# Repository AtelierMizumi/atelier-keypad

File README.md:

# Atelier6K Keypad Project
The Atelier6K is a 6 keys keypad with 3 additional button designed for playing osu! or to be used as small macropad
+ Hotswapable
+ Per switch RGB + Bottom Case RGB
+ Acrylic Case
+ QMK Firmware with VIA compable (Keybinding, Light Control ...)

# Preview images

## PCB front view

## PCB back view

## Case

+ 7$: Fuse, Led, Switch, Bolts, Keycap, USB C Female connector, Rubber Feet
+ 5$: Atmega32u4
+ 5$: Acrylic Case
+ 3$: PCB printing
+ 2$: USB Cable

$40 to be expected

# Sketch

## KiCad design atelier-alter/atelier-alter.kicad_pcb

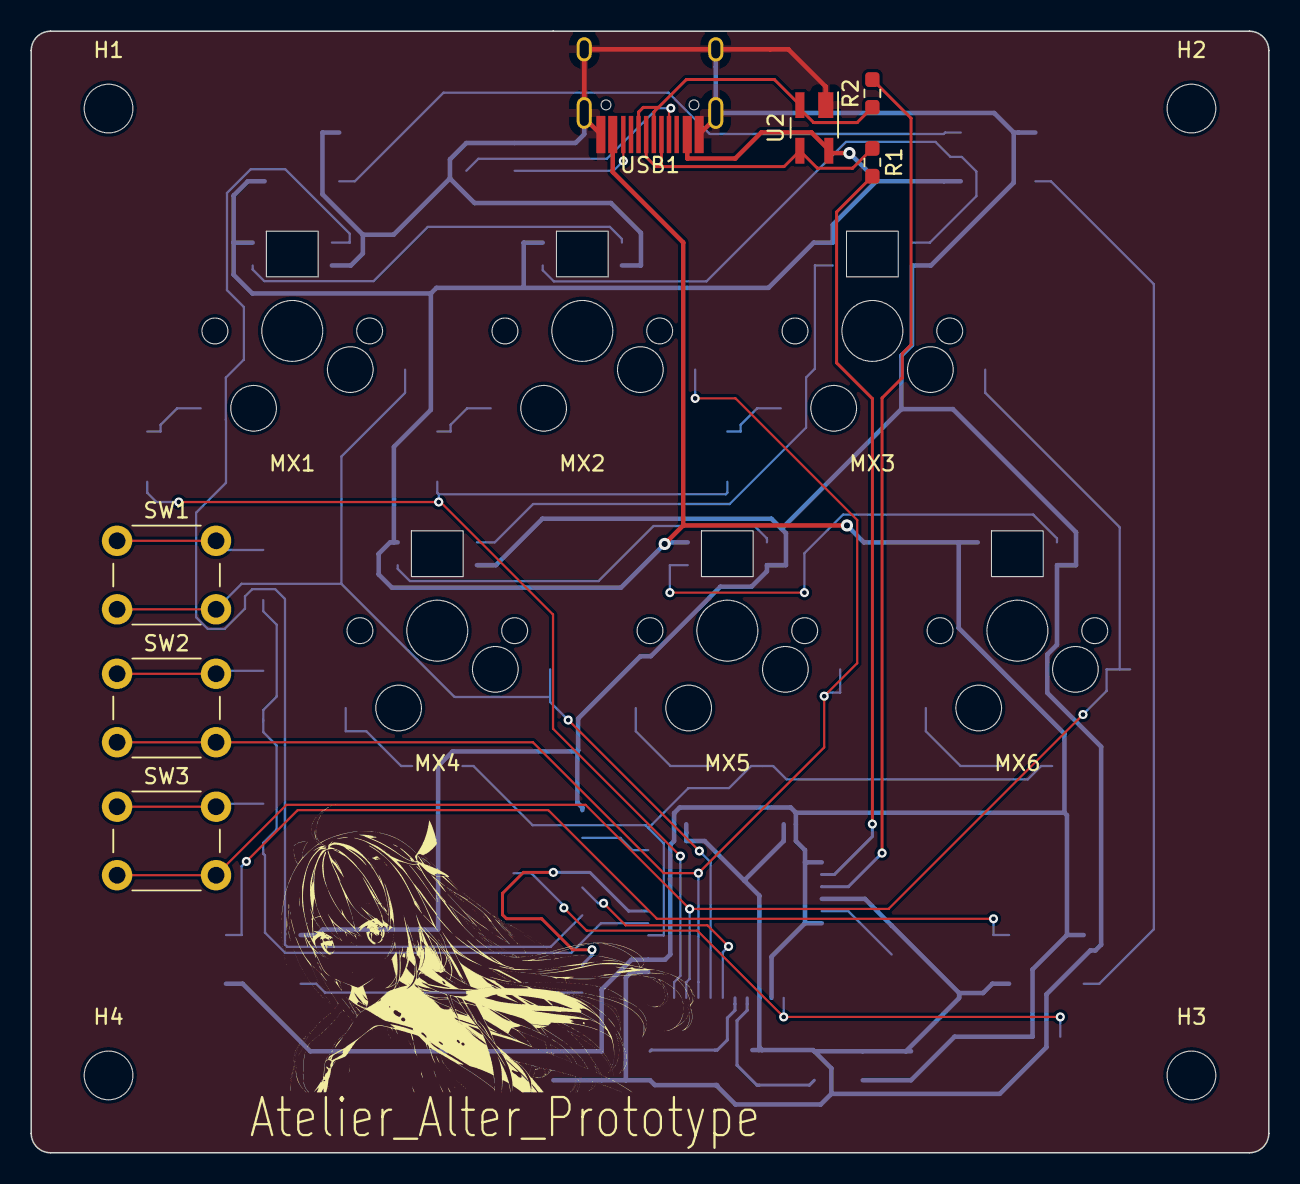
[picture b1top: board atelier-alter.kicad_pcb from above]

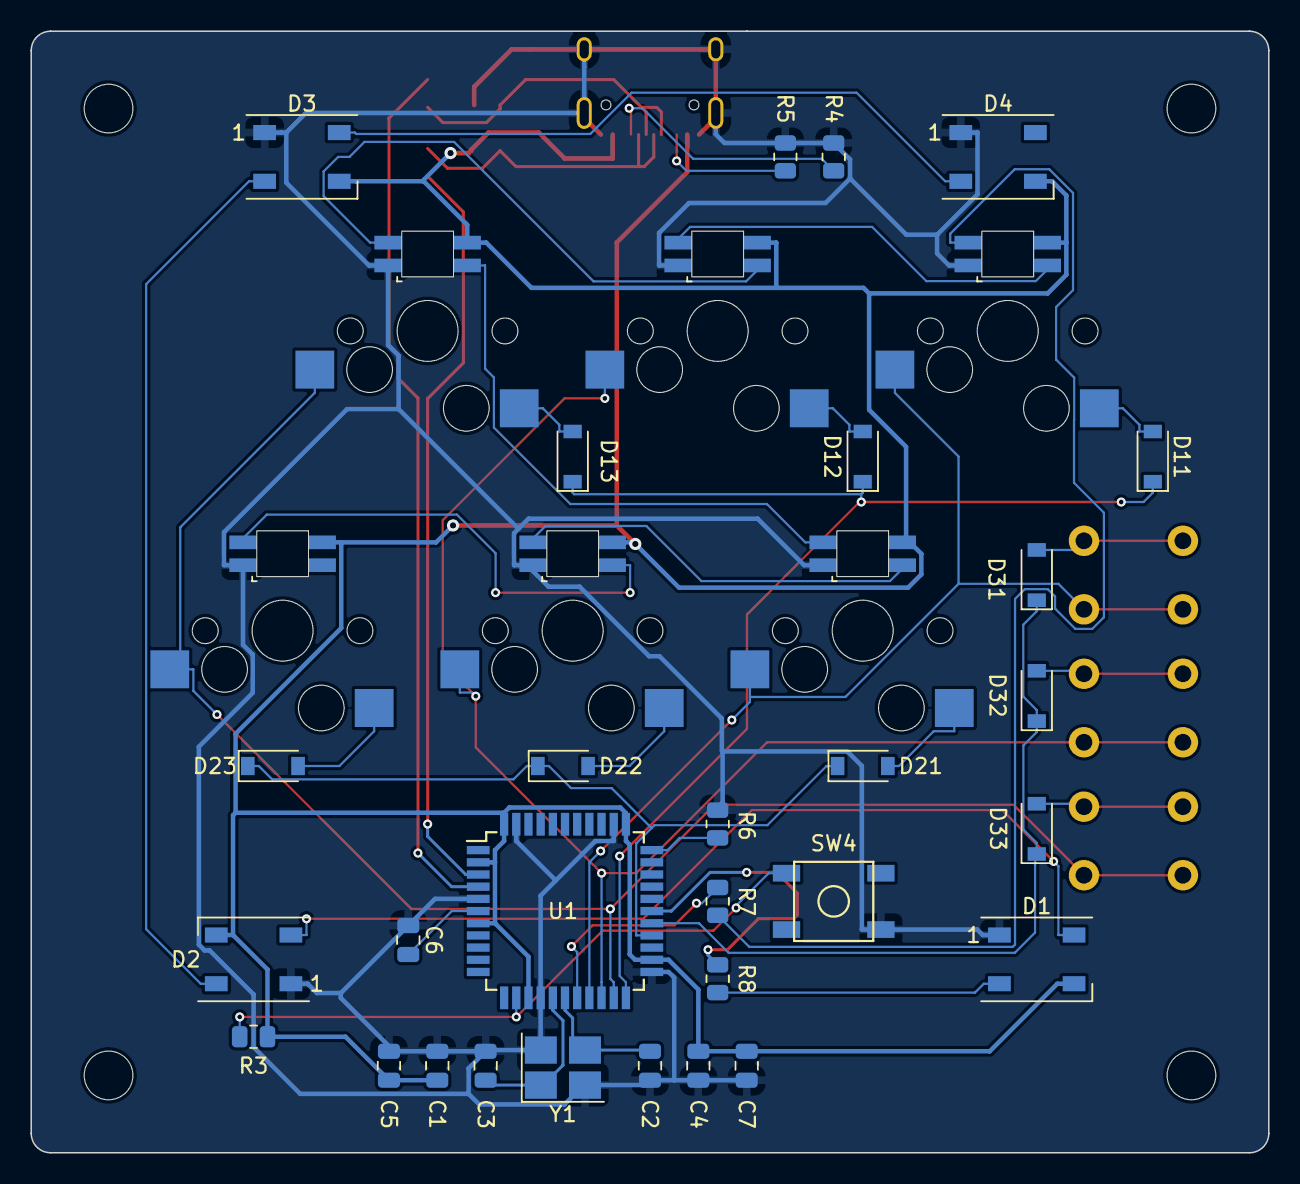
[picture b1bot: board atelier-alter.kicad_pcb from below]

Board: 2 copper layers, 81.3 x 73.7 mm, 47 parts (29 on the bottom side), 40 nets.

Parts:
Atorie': LOGO; Alter_Drawing
C1, C4, C5: 0.1uF; C_0805_2012Metric
C2, C3: 22pF; C_0805_2012Metric
C6: 1uF; C_0805_2012Metric
C7: 10uF; C_0805_2012Metric
D1, D2, D3, D4: SK6812 / WS2812B; LED_WS2812B_PLCC4_5.0x5.0mm_P3.2mm
D11, D12, D13, D21, D22, D23, D31, D32, D33: SOD-123; D_SOD-123
H1, H2, H3, H4: MountingHole; MountingHole_3.2mm_M3_ISO7380
MX1, MX2, MX3, MX4, MX5, MX6: Cherry_MX_Cherry_MX_RGB; Cherry-MX_PCB-Mounted_LTST-A683CEGBW_Kailh_Socket
R1, R2: 22; R_0603_1608Metric_Pad0.98x0.95mm_HandSolder
R3, R6: 10k; R_0805_2012Metric
R4, R5: 5.1k; R_0805_2012Metric
R7, R8: 300; R_0805_2012Metric
SW1, SW2, SW3: SW_DPST; SW_PUSH_6mm_H13mm
SW4: RESET; SKQG-1155865
U1: ATmega32U4-A; TQFP-44_10x10mm_P0.8mm
U2: PRTR5V0U2X; SOT-143_Handsoldering
USB1: HRO-TYPE-C-31-M-12; HRO-TYPE-C-31-M-12-HandSoldering
Y1: 16Mhz; Crystal_SMD_3225-4Pin_3.2x2.5mm_HandSoldering

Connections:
+5V: C1.1, C4.1, C5.1, C7.1, D1.3 (VDD), D2.3 (VDD), D3.3 (VDD), D4.3 (VDD), MX1.4 (VCC), MX2.4 (VCC), MX3.4 (VCC), MX4.4 (VCC), MX5.4 (VCC), MX6.4 (VCC), R3.2, U1.2 (UVCC), U1.7 (VBUS), U1.14 (VCC), U1.24 (AVCC), U1.34 (VCC), U1.44 (AVCC), U2.4 (VCC), USB1.2 (VBUS), USB1.11 (VBUS)
BackRGB: D1.2 (DIN), R8.2
COL1: MX1.5 (SW1), MX4.5 (SW1), SW1.2, U1.19 (PD1)
COL2: MX2.5 (SW1), MX5.5 (SW1), SW2.2, U1.20 (PD2)
COL3: MX3.5 (SW1), MX6.5 (SW1), SW3.2, U1.21 (PD3)
D12: MX3.3 (DOUT), MX4.2 (DIN)
D+: R2.1, U2.2 (IO1), USB1.6 (DP1), USB1.8 (DP2)
D-: R1.1, U2.3 (IO2), USB1.5 (DN2), USB1.7 (DN1)
GND: C1.2, C2.1, C3.1, C4.2, C5.2, C6.1, C7.2, D1.1 (VSS), D2.1 (VSS), D3.1 (VSS), D4.1 (VSS), MX1.1 (GND), MX2.1 (GND), MX3.1 (GND), MX4.1 (GND), MX5.1 (GND), MX6.1 (GND), R4.1, R5.1, R6.2, SW4.1, U1.5 (UGND), U1.15 (GND), U1.23 (GND), U1.35 (GND), U1.43 (GND), U2.1 (GND), USB1.1 (GND), USB1.12 (GND), USB1.13 (SHIELD), Y1.2, Y1.4
InKeyRGB: MX1.2 (DIN), R7.2
unnamed: C2.2, U1.17 (XTAL1), Y1.3
unnamed: C3.2, U1.16 (XTAL2), Y1.1
unnamed: C6.2, U1.6 (UCAP)
unnamed: D1.4 (DOUT), D2.2 (DIN)
unnamed: D2.4 (DOUT), D3.2 (DIN)
unnamed: D3.4 (DOUT), D4.2 (DIN)
unnamed: D11.2 (A), MX1.6 (SW2)
unnamed: D12.2 (A), MX2.6 (SW2)
unnamed: D13.2 (A), MX3.6 (SW2)
unnamed: D21.2 (A), MX4.6 (SW2)
unnamed: D22.2 (A), MX5.6 (SW2)
unnamed: D23.2 (A), MX6.6 (SW2)
unnamed: D31.2 (A), SW1.1
unnamed: D32.2 (A), SW2.1
unnamed: D33.2 (A), SW3.1
unnamed: MX1.3 (DOUT), MX2.2 (DIN)
unnamed: MX2.3 (DOUT), MX3.2 (DIN)
unnamed: MX4.3 (DOUT), MX5.2 (DIN)
unnamed: MX5.3 (DOUT), MX6.2 (DIN)
unnamed: R1.2, U1.3 (D-)
unnamed: R2.2, U1.4 (D+)
unnamed: R3.1, SW4.2, U1.13 (~RESET)
unnamed: R4.2, USB1.4 (CC1)
unnamed: R5.2, USB1.10 (CC2)
unnamed: R6.1, U1.33 (~HWB/PE2)
unnamed: R7.1, U1.18 (PD0)
unnamed: R8.1, U1.28 (PB4)
ROW1: D11.1 (K), D12.1 (K), D13.1 (K), U1.22 (PD5)
ROW2: D21.1 (K), D22.1 (K), D23.1 (K), U1.26 (PD6)
ROW3: D31.1 (K), D32.1 (K), D33.1 (K), U1.27 (PD7)

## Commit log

2022-05-25 get go
2022-05-25 add files
2022-05-25 add submodules
2022-05-25 add main things
2022-05-26 redrawn
2022-05-26 da route thu nghiem xong xuoi
2022-05-27 redrawn lan 3, them vai chuc nang
2022-05-27 tham khao them tu board vcl6k
2022-05-27 kaka, rat manh
2022-05-27 add essentials
2022-05-27 phai them cai db nay moi chiu
2022-05-27 update footprint, route lai mach, giam manh so luong vias
2022-05-27 xuat file gerber de in
2022-05-27 doc tao . md
2022-05-27 get go #2
2022-05-28 add M2 mounting hole
2022-05-28 rework mot chut
2022-05-28 update doc tao di . md
2022-05-28 xuat file gerber dong bo
2022-05-29 doc tao . md and stuff
2022-05-31 small tweaks, done drawing the case
2022-06-02 minor updates here and there
2022-06-03 decided to nuke all led capacitor
2022-06-03 van la doc tao . md
2022-06-04 add qmp firmware files
2022-06-04 update pcb + qmk firmware
2022-06-18 final commit for rev 0.
2022-06-18 final
